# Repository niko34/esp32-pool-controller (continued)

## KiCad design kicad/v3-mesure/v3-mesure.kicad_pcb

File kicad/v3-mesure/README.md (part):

# Carte de mesure du PCB v3 — composants et connexions

> **État : schéma (révision 0.7) et carte routée par script, relus par le relecteur**
> **— toutes les empreintes attribuées, ⚠️ pas encore relu par le relecteur.** Aucune carte n'est dessinée. Ce document est la référence contre
> laquelle le schéma, puis la carte, sont relus.
> Fiche de conception : [`feature-215`](../../specs/features/todo/feature-215-conception-du-pcb-v3.md) ·
> contraintes de fabrication : [`docs/FABRICATION.md`](../../docs/FABRICATION.md).
> Dernière mise à jour : 2026-11-24.

## Les fichiers de ce dossier

| Fichier | Rôle |
|---|---|
| `v3-mesure.kicad_pro` | projet KiCad 9 — c'est lui qu'on ouvre |
| `v3-mesure.kicad_sch` | le schéma, une seule feuille A3 |
| `v3-mesure.kicad_sym` + `sym-lib-table` | les quatre symboles propres à cette carte : ADM3260, module Atlas OEM, prise BNC, connecteur 8 voies |
| `v3-mesure.pretty/` + `fp-lib-table` | les trois empreintes propres à cette carte : `Atlas_OEM`, `BNC_Dosin_801-0080_Coudee`, `Trou_M3_NPTH` |
| `v3-mesure.kicad_pcb` | la carte, **placée et routée** |
| `generer_carte.py` | le script qui écrit la carte ; il prend en entrée la liste des connexions exportée du schéma |
| `v3-mesure.kicad_dru` | la règle d'isolement entre les trois domaines |
| `generer_schema.py` | le script qui a écrit le schéma depuis le tableau des connexions |

**Le schéma (révision 0.7) est tracé avec de vrais fils** — demande de l'utilisateur du
2026-11-24, la révision 0.1 reliait tout par étiquettes. Les alimentations et les masses
passent par les symboles habituels (flèche, masse), comme dans le schéma du v2. Seuls les
quatre signaux du bus rejoignent le connecteur J1 par étiquette, parce que J1 est commun aux
deux voies.

**Ce qui a été vérifié**
- **Dans le KiCad de l'utilisateur** (révision 0.1, 2026-11-24) : contrôle électrique à
  **0 erreur, 0 avertissement**. ⇒ Les noms d'empreintes standard (0402, 0805, 0603,
  SSOP-20, JST XH) existent bien dans ses bibliothèques.
- **En ligne de commande** (révision 0.7, KiCad 9.0.2) : 0 erreur ; la liste des connexions
  que KiCad extrait du schéma est **identique** à celle du tableau de ce document — 21 nets,
  12 broches volontairement en l'air ; rendu regardé en image, sans chevauchement.
  Sur ce poste, le contrôle rend des avertissements d'un seul type : les bibliothèques
  standard de KiCad n'y sont pas installées.

**Ce qui n'est PAS vérifié**
- ✅ Révision 0.2 ouverte dans le KiCad de l'utilisateur le 2026-11-24 : contrôle électrique sans problème. ⚠️ Les révisions 0.3 (C108/C208 retirés) à 0.5 (empreintes du module et de la BNC attribuées) n'y ont pas encore été ouvertes.
- ⚠️ **Aucune des deux empreintes propres n'a été confrontée à une pièce réelle** : elles
  suivent les plans publiés. Avant de commander la carte, imprimer le routage à l'échelle 1
  et y poser un module Atlas et une prise BNC.

⚠️ **`generer_schema.py` réécrit le schéma en entier.** Dès que le schéma est modifié à la
main dans KiCad, ⛔ ne plus le relancer : il écraserait ces modifications.
ℹ️ Le script contient un piège appris à l'usage : KiCad ne relie un fil à un point que si le
fil **s'arrête** à ce point. Un fil qui passe sur une broche sans s'y arrêter n'est pas
relié, même avec un point de jonction dessiné. Le script coupe donc chaque fil à chaque
point de connexion.

## Disposition dans le boîtier (utilisateur, 2026-11-24)

**La carte est montée à l'horizontale (« paysage ») et les prises BNC sortent par le bas.**
⇒ Les deux BNC sont sur le **grand bord du bas**, et ce sont des prises **coudées**.

Conséquences pour le placement, à tenir au routage :
- chaque module Atlas est tourné pour que ses broches 4 (`PRB`) et 5 (`PRB_GND`) regardent
  **vers le bas**, face à sa BNC : c'est ce qui garde la piste de sonde courte ;
- le plan `GND_SONDE` de chaque voie occupe la zone entre le module et le bord du bas
  (Atlas, p. 33 : le plan de sonde couvre le coin des broches 4 et 5) ;
- le connecteur J1 et le côté ESP32 sont à l'opposé, vers le haut ou le centre ;
- ⚠️ le corps des BNC traverse la paroi du bas : **paroi isolante, ou trou plus large que le
  corps** — il ne doit toucher aucun métal relié à la terre (voir « Relecture »).

**Prise retenue** : `C521219` — dosinconn **DOSIN-801-0080**, « BNC jack for PCB », 50 Ω,
coudée, traversante, pièce étendue chez JLCPCB (2 832 en stock chez le distributeur le
2026-11-24). Plan du fabricant (révision A) lu le 2026-11-24 :

| Ce que dit le plan | Valeur |
|---|---|
| Genre | embase femelle (« jack ») ✅ |
| Corps | **laiton nickelé — donc métallique** ; isolant en téflon |
| Fixation | nez **fileté M12 × 0,75**, avec écrou et joint : la prise se **serre sur la paroi** |
| Pattes de corps | 4, Ø 1,2 mm, au pas de **8 mm** (le long de l'axe) × **10 mm** (en travers) |
| Âme | Ø 1 mm, au centre des quatre pattes |
| Hauteur de l'axe au-dessus de la carte | 9,8 mm |
| Longueur totale | 29,5 mm |

⚠️ **Conséquence directe pour le boîtier** : la prise est faite pour être serrée par son écrou
sur la paroi, et son corps est en métal. ⇒ **La paroi du bas doit être isolante** (plastique).
Sur une paroi métallique reliée à la terre, le serrage relierait `GND_SONDE` à la terre et
les deux voies entre elles : l'isolation serait annulée. Le joint, lui, est une bonne chose
en local humide.

**Empreinte** : `v3-mesure:BNC_Dosin_801-0080_Coudee`, nez vers le bas. Âme = plot 1 ; les
quatre pattes de corps = plot 2 (`GND_SONDE`). ✅ Les positions des cinq trous viennent des
cotes écrites sur le plan. ⚠️ Le contour du corps et la position de la paroi (≈ 6,7 mm de
l'âme) sont **mesurés sur le dessin**, pas cotés : à vérifier pièce en main. ⚠️ Perçages
choisis par moi : 1,5 mm pour les pattes, 1,3 mm pour l'âme.

## Dimensions et zones de la carte (proposition du 2026-11-24)

**Règle donnée par l'utilisateur** : le boîtier actuel sert à l'idée générale de disposition ;
les tailles des cartes se fixent librement ; **le boîtier sera adapté ensuite** aux cartes.

**Carte de mesure : 70 × 50 mm, quatre couches, 1,6 mm.** Grand côté à l'horizontale, les
deux BNC sur le bord du bas.

```
        0        17      35      53       70 mm
      0 +----------------------------------+
        | o   COTE ESP32 : J1 au centre  o |   bande de 12 mm :
        |     C101-C104, R101-R102 (x2)    |   connecteur, découplage, rappels
     12 +- - - -[U101]- - - - -[U201]- - - +
        |       barrière : 5,5 mm sans     |   les deux ADM3260 à cheval dessus
   17,5 +- - - - - - - -+   +- - - - - - - +
        |  ILE pH        | | |  ILE ORP    |   5,5 mm sans cuivre entre les îles
        |  C105-C107     | | |  C205-C207  |
        |  R103-R106     | | |  R203-R206  |
        |  [U102 Atlas]  | | |  [U202]     |
        | o [J101 BNC]   | | |  [J201]   o |
     50 +------|---------+---+----|--------+
              16,85             53,15         axes des BNC : entraxe 36,3 mm
```

| Élément | Valeur | Pourquoi |
|---|---|---|
| Largeur | 70 mm | deux îles de 30,8 mm + 5,5 mm entre elles + 1,45 mm de marge de chaque côté |
| Hauteur | 50 mm | bande ESP32 12 mm + barrière 5,5 mm + îles 32,5 mm |
| Entraxe des BNC | **36,3 mm** | celui des deux perçages existants du boîtier : ils peuvent resservir |
| Axe des BNC | à X = 16,85 et 53,15 mm | centre de chaque île |
| Âme des BNC | à 6,0 mm du bord du bas | la paroi intérieure est à ≈ 6,7 mm de l'âme : 0,7 mm de jeu entre carte et paroi |
| Barrière | bande sans cuivre de 5,5 mm, de Y = 12 à 17,5 mm | fiche ADM3260 rév. F ; les deux isolateurs la chevauchent |
| Séparation des voies | bande sans cuivre de 5,5 mm, de X = 32,25 à 37,75 mm | les deux voies ne partagent rien |
| Fixations | 4 trous Ø 3,2 mm **non métallisés**, à 3,5 mm des bords | reliés à rien (relecture) ; cuivre écarté de 2 mm autour |

**Dans chaque île, de haut en bas** : la moitié isolée de l'ADM3260 et ses sept composants ;
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
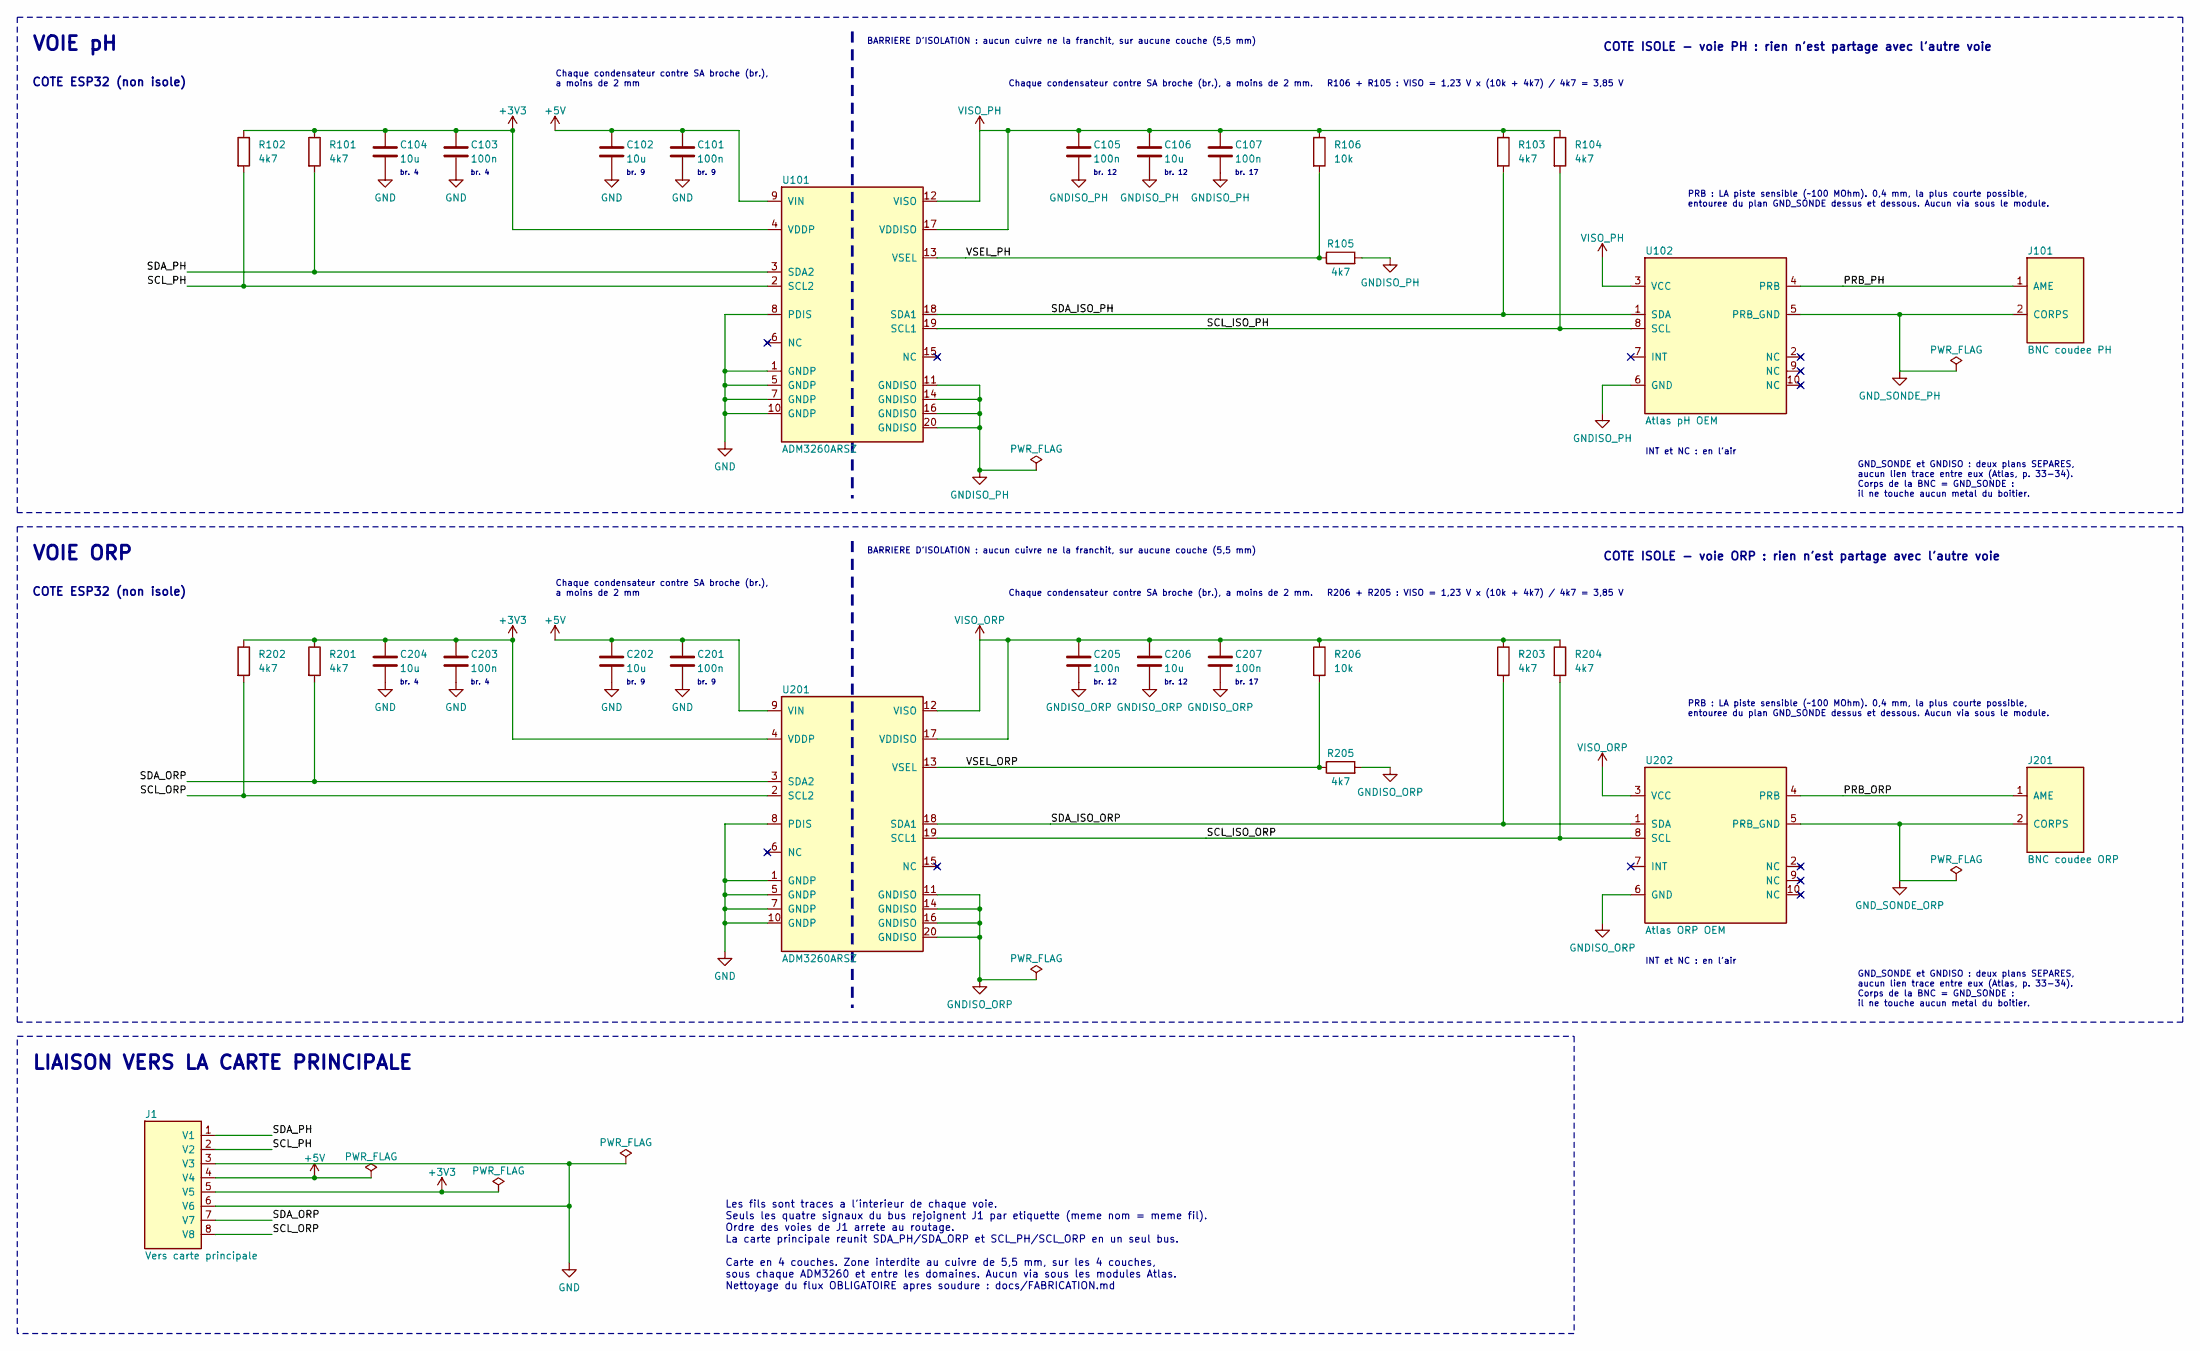
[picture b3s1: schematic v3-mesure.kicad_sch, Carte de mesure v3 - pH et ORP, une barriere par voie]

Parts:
C101, C103, C105, C107, C201, C203, C205, C207: 100n; C_0402_1005Metric; LCSC C1525
C102, C104, C106, C202, C204, C206: 10u; C_0805_2012Metric; LCSC C15850
J1: Vers carte principale; JST_XH_B8B-XH-A_1x08_P2.50mm_Vertical; LCSC C157972
J101: BNC coudee PH; BNC_Dosin_801-0080_Coudee; LCSC C521219
J201: BNC coudee ORP; BNC_Dosin_801-0080_Coudee; LCSC C521219
R101, R102, R103, R104, R105, R201, R202, R203, R204, R205: 4k7; R_0603_1608Metric; LCSC C23162
R106, R206: 10k; R_0603_1608Metric; LCSC C25804
U101, U201: ADM3260ARSZ; SSOP-20_5.3x7.2mm_P0.65mm; LCSC C208558
U102: Atlas pH OEM; Atlas_OEM
U202: Atlas ORP OEM; Atlas_OEM

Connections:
+3V3: C103.1, C104.1, C203.1, C204.1, J1.5 (V5), R101.1, R102.1, R201.1, R202.1, U101.4 (VDDP), U201.4 (VDDP)
+5V: C101.1, C102.1, C201.1, C202.1, J1.4 (V4), U101.9 (VIN), U201.9 (VIN)
/PRB_ORP: J201.1 (AME), U202.4 (PRB)
/PRB_PH: J101.1 (AME), U102.4 (PRB)
/SCL_ISO_ORP: R204.2, U201.19 (SCL1), U202.8 (SCL)
/SCL_ISO_PH: R104.2, U101.19 (SCL1), U102.8 (SCL)
/SCL_ORP: J1.8 (V8), R202.2, U201.2 (SCL2)
/SCL_PH: J1.2 (V2), R102.2, U101.2 (SCL2)
/SDA_ISO_ORP: R203.2, U201.18 (SDA1), U202.1 (SDA)
/SDA_ISO_PH: R103.2, U101.18 (SDA1), U102.1 (SDA)
/SDA_ORP: J1.7 (V7), R201.2, U201.3 (SDA2)
/SDA_PH: J1.1 (V1), R101.2, U101.3 (SDA2)
/VSEL_ORP: R205.1, R206.2, U201.13 (VSEL)
/VSEL_PH: R105.1, R106.2, U101.13 (VSEL)
GND: C101.2, C102.2, C103.2, C104.2, C201.2, C202.2, C203.2, C204.2, J1.3 (V3), J1.6 (V6), U101.1 (GNDP), U101.5 (GNDP), U101.7 (GNDP), U101.8 (PDIS), U101.10 (GNDP), U201.1 (GNDP), U201.5 (GNDP), U201.7 (GNDP), U201.8 (PDIS), U201.10 (GNDP)
GNDISO_ORP: C205.2, C206.2, C207.2, R205.2, U201.11 (GNDISO), U201.14 (GNDISO), U201.16 (GNDISO), U201.20 (GNDISO), U202.6 (GND)
GNDISO_PH: C105.2, C106.2, C107.2, R105.2, U101.11 (GNDISO), U101.14 (GNDISO), U101.16 (GNDISO), U101.20 (GNDISO), U102.6 (GND)
GND_SONDE_ORP: J201.2 (CORPS), U202.5 (PRB_GND)
GND_SONDE_PH: J101.2 (CORPS), U102.5 (PRB_GND)
VISO_ORP: C205.1, C206.1, C207.1, R203.1, R204.1, R206.1, U201.12 (VISO), U201.17 (VDDISO), U202.3 (VCC)
VISO_PH: C105.1, C106.1, C107.1, R103.1, R104.1, R106.1, U101.12 (VISO), U101.17 (VDDISO), U102.3 (VCC)

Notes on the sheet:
VOIE pH
COTE ESP32 (non isole)
COTE ISOLE - voie PH : rien n'est partage avec l'autre voie
BARRIERE D'ISOLATION : aucun cuivre ne la franchit, sur aucune couche (5,5 mm)
br. 9
br. 4
Chaque condensateur contre SA broche (br.), a moins de 2 mm
br. 12
br. 17
PRB : LA piste sensible (~100 MOhm). 0,4 mm, la plus courte possible, entouree du plan GND_SONDE dessus et dessous. Aucun via sous le module.
GND_SONDE et GNDISO : deux plans SEPARES, aucun lien trace entre eux (Atlas, p. 33-34). Corps de la BNC = GND_SONDE : il ne touche aucun metal du boitier.
INT et NC : en l'air
Chaque condensateur contre SA broche (br.), a moins de 2 mm. R106 + R105 : VISO = 1,23 V x (10k + 4k7) / 4k7 = 3,85 V
VOIE ORP
COTE ISOLE - voie ORP : rien n'est partage avec l'autre voie
Chaque condensateur contre SA broche (br.), a moins de 2 mm. R206 + R205 : VISO = 1,23 V x (10k + 4k7) / 4k7 = 3,85 V
LIAISON VERS LA CARTE PRINCIPALE
Les fils sont traces a l'interieur de chaque voie. Seuls les quatre signaux du bus rejoignent J1 par etiquette (meme nom = meme fil). Ordre des voies de J1 arrete au routage. La carte principale reunit SDA_PH/SDA_ORP et SCL_PH/SCL_ORP en un seul bus. Carte en 4 couches. Zone interdite au cuivre de 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

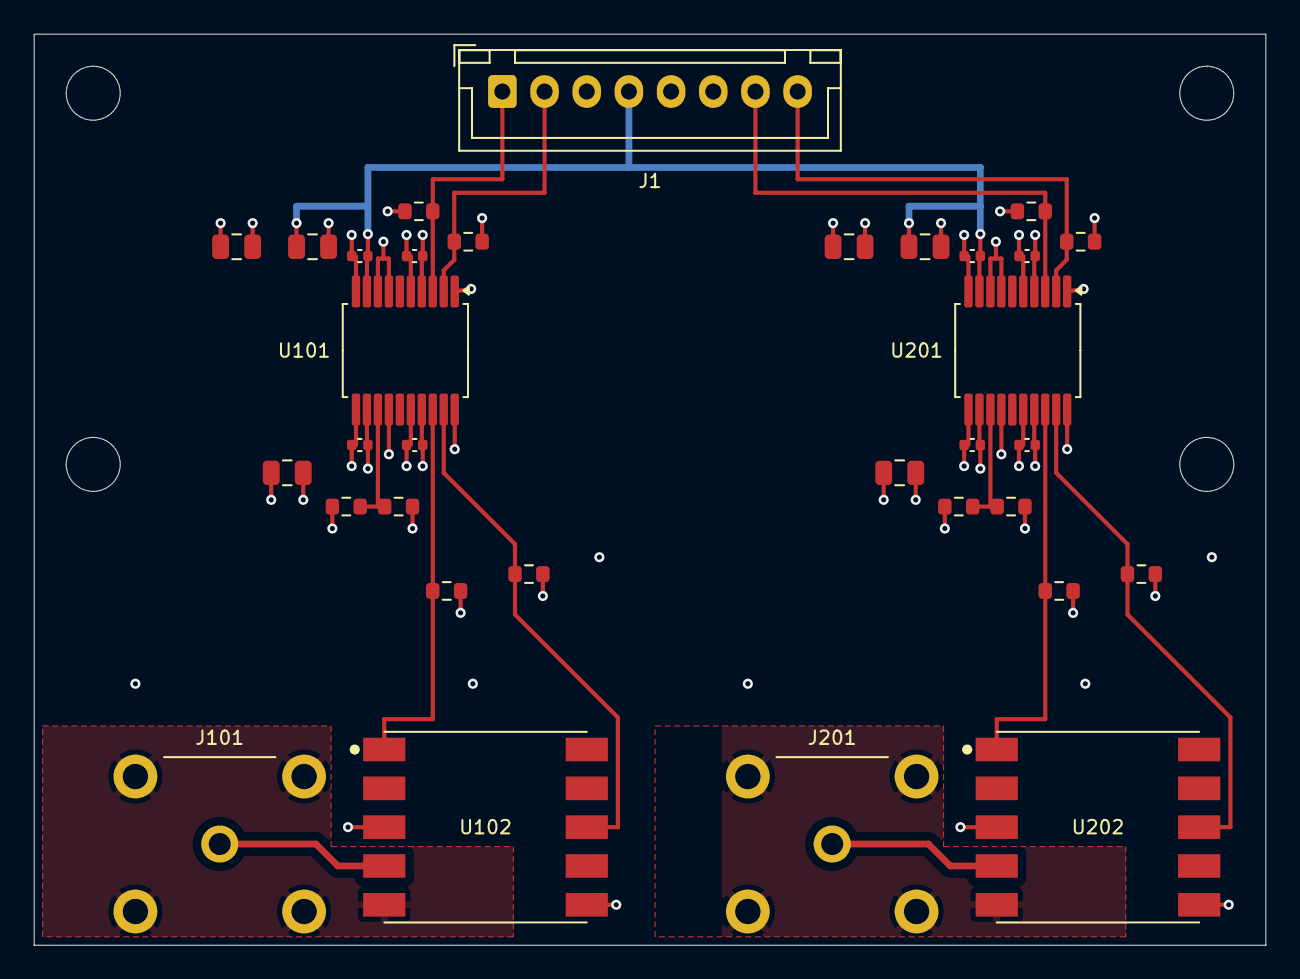
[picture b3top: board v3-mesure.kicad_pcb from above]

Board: 4 copper layers, 73.0 x 54.0 mm, 37 parts (0 on the bottom side), 21 nets.

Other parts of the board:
H1, H2, H3, H4: Trou_M3_NPTH

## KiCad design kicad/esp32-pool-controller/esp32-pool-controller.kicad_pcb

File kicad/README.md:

# Matériel — point d'entrée

Sources KiCad du PCB du contrôleur de piscine.

⚠️ **Les sources de ce dossier sont GELÉES sauf demande explicite** (règle 5 de
[`CLAUDE.md`](../CLAUDE.md)) : on ne modifie ni le schéma ni le routage au fil
d'une tâche logicielle.

⭐ **Avant de modifier une carte du v3** (`v3-principale/`, `v3-mesure-std/`) : lire
[`REGLES-CEM-ET-FIABILITE.md`](REGLES-CEM-ET-FIABILITE.md). Il dit quelles protections chaque
carte porte, pourquoi, et ce qui a déjà été étudié puis écarté. Après la modification :
`python3 scripts/verifier_regles_cartes.py <carte>` — `./scripts/build-jlcpcb.sh` le lance d'office
et refuse de produire les fichiers de fabrication si une règle tombe.

## Fichiers

| Fichier | Rôle |
|---|---|
| `esp32-pool-controller.kicad_sch` · `.kicad_pcb` · `.kicad_pro` | Sources, **versionnées** |
| `SymLib.kicad_sym` · `sym-lib-table` | Bibliothèque de symboles du projet |
| `BOM.xlsx` | **Nomenclature de référence** — ⛔ toute correction se fait ICI |

⛔ **`BOM.csv` est un DÉRIVÉ**, généré par `python3 tools/bom_export.py` depuis le
`.xlsx`, donc ignoré par git. ⚠️ **Ne jamais le corriger à la main** : la prochaine
exécution du script l'écrase.

Les fichiers de fabrication (gerbers, perçage, zips) ne sont **pas** versionnés :
ils se régénèrent avec `./scripts/build-gerbers.sh` (carte v2) ou `./scripts/build-jlcpcb.sh` (cartes v3, avec la liste des pièces et les positions) et deviennent les assets d'une
release `pcb-vX` via `/release-pcb`.

---

## 🔴 Deux défauts MATÉRIELS non résolus — à instruire avant toute révision du PCB

**Ils ont été sortis du backlog logiciel le 2026-10-17**, sur décision de
l'utilisateur : *« ces investigations sont du ressort de l'humain qui conçoit le
PCB »*. ⛔ **Clôturées ne veut pas dire résolues** — elles attendent une personne
avec des instruments, pas une session de travail.

### 1. Perturbation de mode commun sur les électrodes pH/ORP
[`specs/features/done/feature-137-perturbation-de-mode-commun-sur-les-electrodes.md`](../specs/features/done/feature-137-perturbation-de-mode-commun-sur-les-electrodes.md)

Le pH brut est **anti-corrélé et presque à deux niveaux**, et **la voie ORP voit la
même perturbation** : les deux électrodes subissent un **mode commun**. Mécanisme
suspecté : couplage électrique via le verre (~100 MΩ) avec les **courants de fuite
de la pompe de filtration** — mesure nettement meilleure sur batterie.

⚠️ **Ce que ça coûte aujourd'hui** : le 2026-10-16, l'eau réelle était à **pH 8**
et la sonde lisait **6,9**. Une correction de **+1,00** a dû être posée — **le
double de l'ancienne borne**, retirée pour la rendre possible (ADR-0114, v2.82.0).
⛔ **Le logiciel ne corrige pas ce défaut, il le COMPENSE** — sur la grandeur même
qui décide des injections d'acide.

⇒ C'est la **seule voie** qui assainirait le signal **à la source**.

### 2. Transitoire de reprise de filtration
[`specs/features/done/feature-069-investigation-materielle-sonde-ph.md`](../specs/features/done/feature-069-investigation-materielle-sonde-ph.md)

Trois matins consécutifs (02-04/09/2026), même signature : brut **normal** à la
remise en circulation, plongeon à **5,60-5,71** quelques minutes après, retour à la
normale en **30 à 48 min**, ⚠️ **l'ORP plongeant en parallèle** (−56 à −74 mV).

⛔ **Les cinq hypothèses restent ouvertes** (chambre désamorcée · bulles piégées ·
effet électrique au démarrage · eau réellement acide · sonde vieillissante).

⭐ **Le relevé qui tranche** : **deux bandelettes simultanées**, une au **bassin** et
une au **refoulement**, à **t+2** et **t+15 min** après la reprise. C'est le seul
qui sépare « l'eau est réellement acide » de « la sonde lit faux ». ⚠️ Tout le reste
en découle.
⛔ **Préalable de sécurité** : régulation pH en **manuel** pendant toute
manipulation de sonde.

### Lié, et toujours ouvert côté logiciel
[`bug-135`](../specs/features/todo/bug-135-butee-brute-ph-se-declenche-sur-une-lecture-isolee.md)
— la butée de sécurité brute se déclenche sur ces lectures isolées. ⚠️ **Même
cause** : tant que le mode commun est là, le logiciel doit composer avec un signal
qui alterne entre deux niveaux.

## Références
- [ADR-0012 — mapping GPIO du PCB v2](../docs/adr/0012-mapping-gpio-pcb-v2.md)
- [ADR-0097 — Le filtre lisse, le dosage juge](../docs/adr/0097-le-filtre-lisse-le-dosage-juge.md) — ce que le logiciel fait du bruit, faute de pouvoir le supprimer
- [feature-097 — Seuil de stabilité sur données terrain](../specs/features/done/feature-097-seuil-de-stabilite-sur-donnees-terrain.md) — la campagne qui **caractérise** le bruit (⛔ sans l'expliquer)

Pour passer la commande : [étapes et options JLCPCB](COMMANDE-JLCPCB.md).

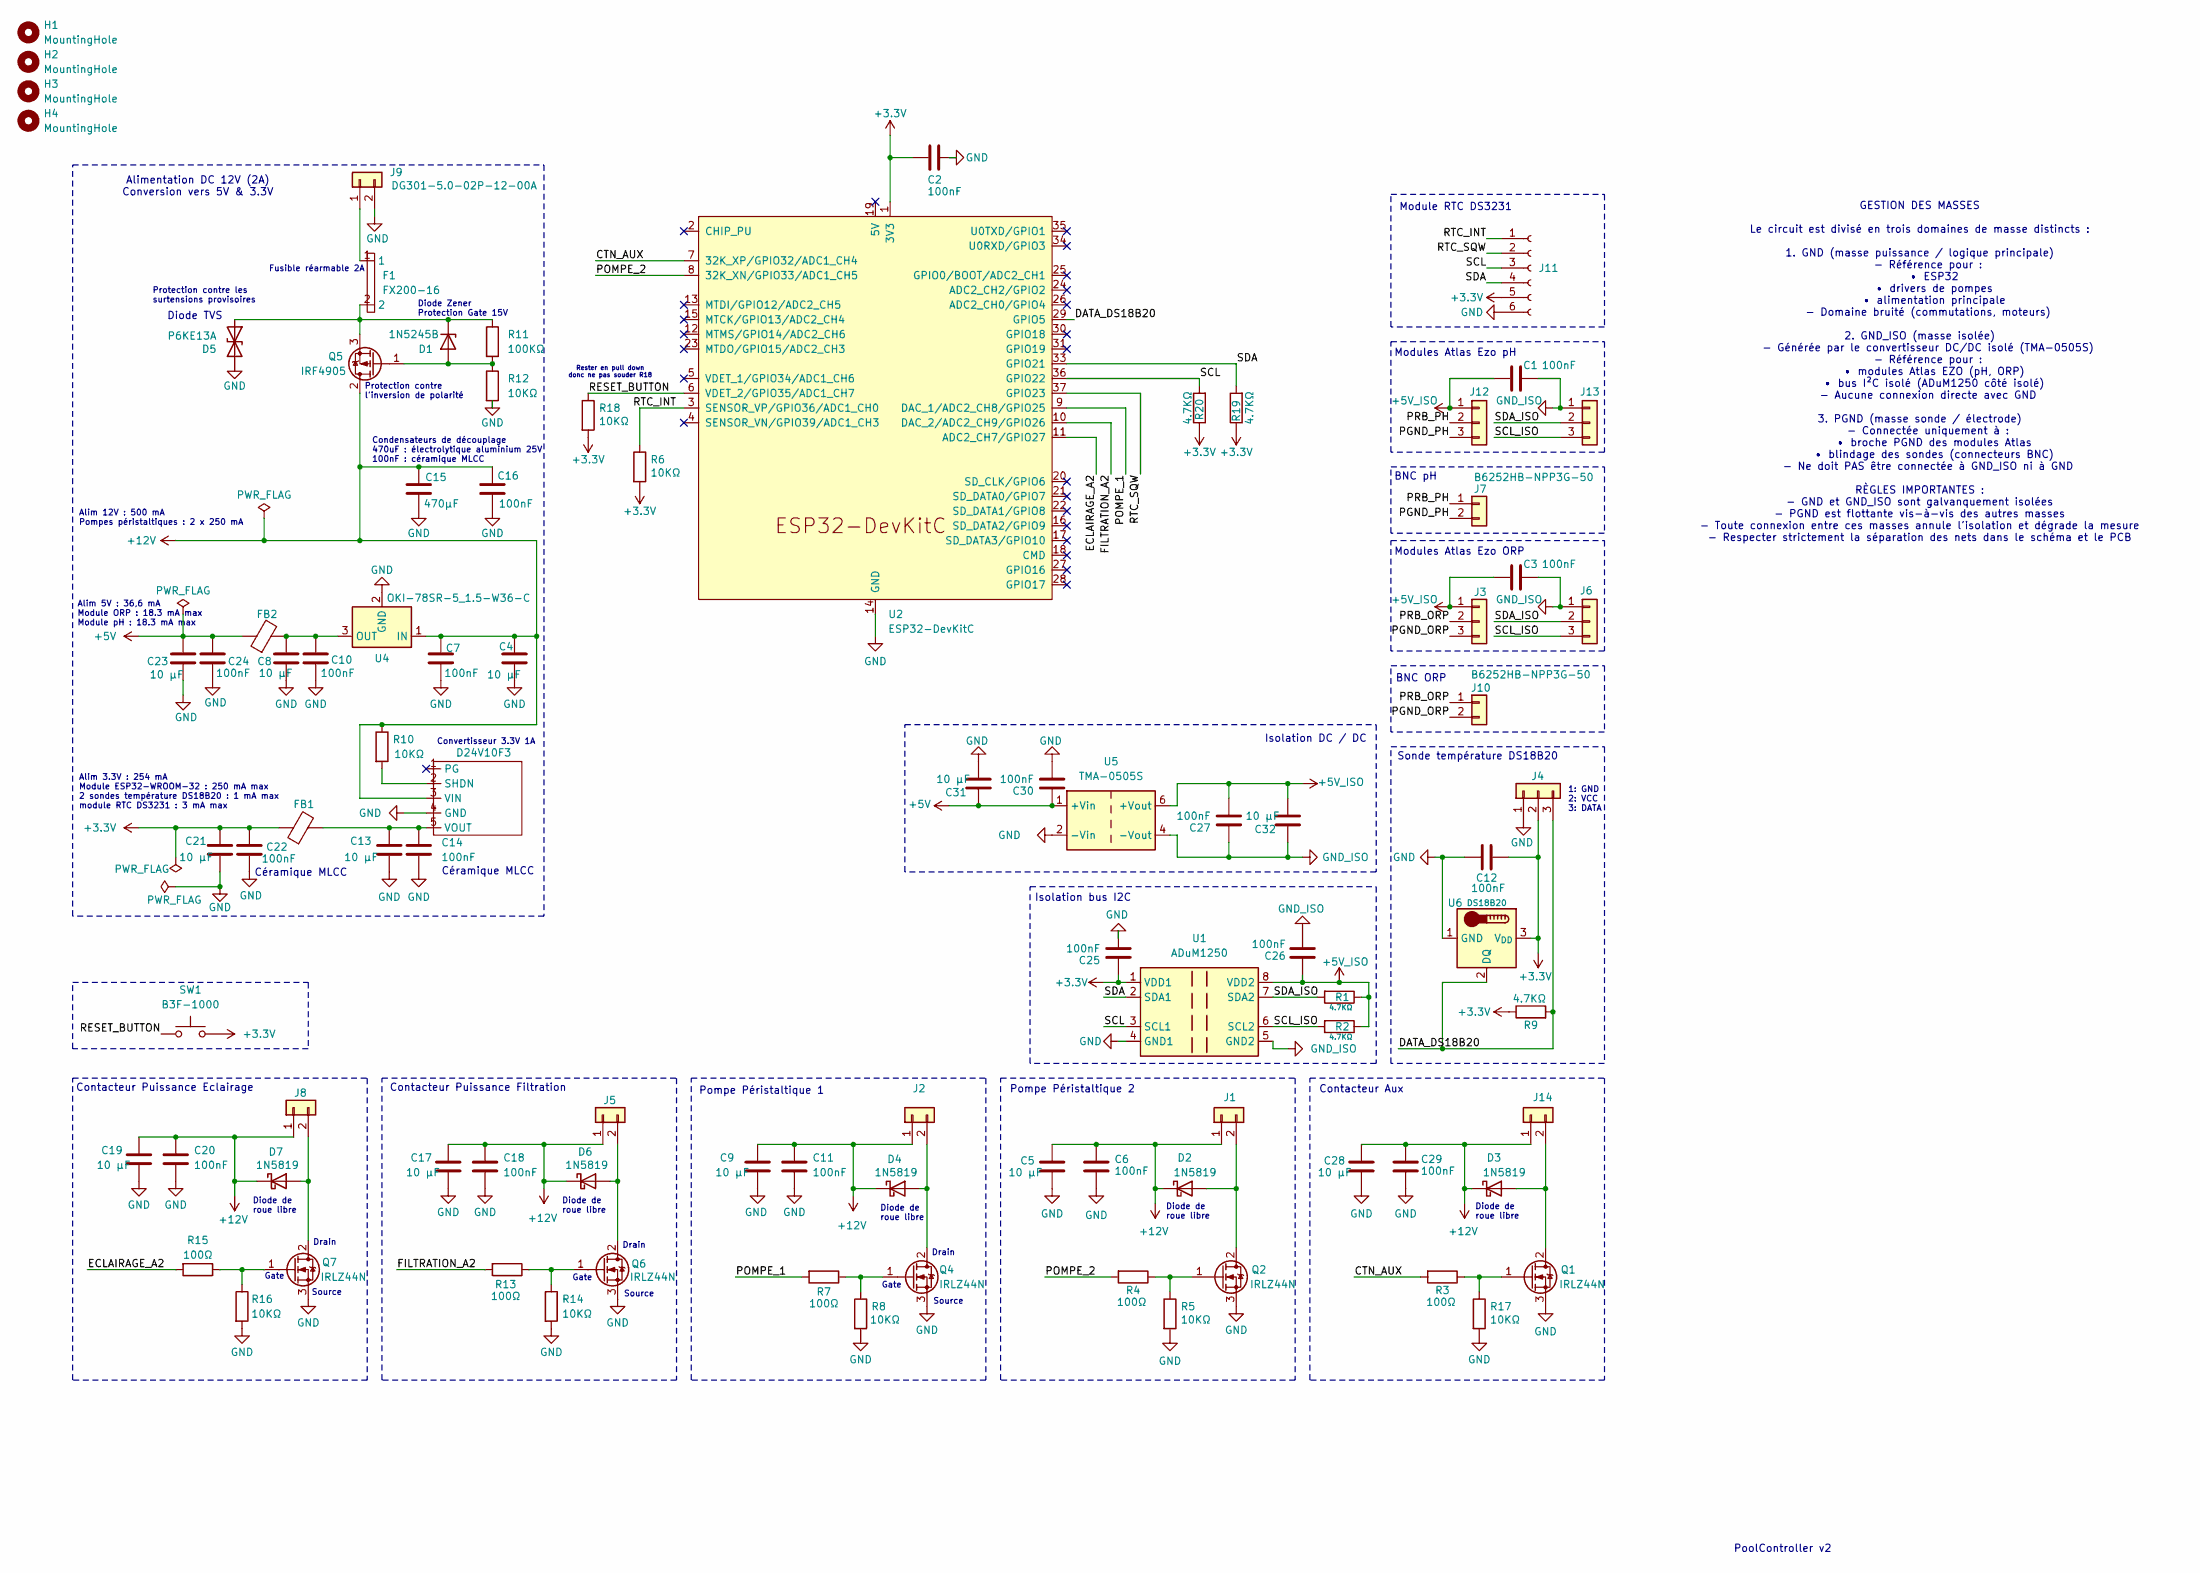
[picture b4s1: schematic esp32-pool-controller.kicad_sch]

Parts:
C1, C2, C3, C6, C7, C10, C11, C12, C14, C16, C18, C20, C22, C24, C25, C26, C27, C29, C30: 100nF; C_Disc_D3.8mm_W2.6mm_P2.50mm
C4, C5, C8, C9, C13, C17, C19, C21, C23, C28, C31, C32: 10 µF; C_Disc_D6.0mm_W4.4mm_P5.00mm
C15: 470µF; CP_Radial_D10.0mm_P5.00mm
D1: 1N5245B; D_DO-35_SOD27_P7.62mm_Horizontal
D2, D3, D4, D6, D7: 1N5819; D_DO-15_P10.16mm_Horizontal
D5: P6KE13A; D_DO-15_P10.16mm_Horizontal
F1: FX200-16; Fuse_Bourns_MF-RHT200
FB1, FB2: BBPY00321611601Y00; R_1206_3216Metric
H1, H2, H3, H4: MountingHole; MountingHole_3.2mm_M3
J1, J2, J5, J8, J9, J14: DG301-5.0-02P-12-00A; Altech_AK100_1x02_P5.00mm
J3, J6, J12, J13: Conn_01x03; PinSocket_1x03_P2.54mm_Vertical
J4: DG301-5.0-03P-12-00AH; JST_XH_B3B-XH-A_1x03_P2.50mm_Vertical
J7, J10: B6252HB-NPP3G-50; BNC_Amphenol_B6252HB-NPP3G-50_Horizontal
J11: Conn_01x06_Socket; PinSocket_1x06_P2.54mm_Vertical
Q1, Q2, Q4, Q6, Q7: IRLZ44N; TO-220-3_Vertical
Q5: IRF4905; TO-220-3_Vertical
R1, R2, R9, R19, R20: 4.7KΩ; R_Axial_DIN0207_L6.3mm_D2.5mm_P10.16mm_Horizontal
R3, R4, R7, R13, R15: 100Ω; R_Axial_DIN0207_L6.3mm_D2.5mm_P10.16mm_Horizontal
R5, R6, R8, R10, R12, R14, R16, R17, R18: 10KΩ; R_Axial_DIN0207_L6.3mm_D2.5mm_P10.16mm_Horizontal
R11: 100KΩ; R_Axial_DIN0207_L6.3mm_D2.5mm_P10.16mm_Horizontal
SW1: B3F-1000; SW_PUSH_6mm
U1: ADuM1250; DIP-8_W7.62mm
U2: ESP32-DevKitC
U3: D24V10F3; Pololu_D24V10F3
U4: OKI-78SR-5_1.5-W36-C; Converter_DCDC_Murata_OKI-78SR_Vertical
U5: TMA-0505S; Converter_DCDC_TRACO_TMA-05xxS_12xxS_Single_THT
U6: DS18B20; TO-92_Inline

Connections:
+3.3V: C2.2, C12.2, C21.1, C22.1, C25.1, FB1.1, J4.2, J11.5, R6.2, R9.1, R18.2, R19.1, R20.1, SW1.2, U1.1 (VDD1), U2.1 (3V3), U6.3 (V_{DD})
+5V: C23.1, C24.1, C30.1, C31.2, FB2.1, U5.1 (+Vin)
+5V_ISO: C1.1, C3.1, C26.1, C27.2, C32.1, J3.1, J12.1, R1.1, R2.1, U1.8 (VDD2), U5.6 (+Vout)
+12V: C4.1, C5.1, C6.1, C7.1, C9.1, C11.1, C15.1, C16.1, C17.1, C18.1, C19.1, C20.1, C28.1, C29.1, D2.1 (K), D3.1 (K), D4.1 (K), D6.1 (K), D7.1 (K), J1.1, J2.1, J5.1, J8.1, J14.1, Q5.2 (D), R10.1, U3.3 (VIN), U4.1 (IN)
/CTN_AUX: R3.2, U2.7 (32K_XP/GPIO32/ADC1_CH4)
/DATA_DS18B20: J4.3, R9.2, U2.29 (GPIO5), U6.2 (DQ)
/ECLAIRAGE_A2: R15.2, U2.11 (ADC2_CH7/GPIO27)
/FILTRATION_A2: R13.2, U2.10 (DAC_2/ADC2_CH9/GPIO26)
/PGND_ORP: J3.3, J10.2
/PGND_PH: J7.2, J12.3
/POMPE_1: R7.2, U2.9 (DAC_1/ADC2_CH8/GPIO25)
/POMPE_2: R4.2, U2.8 (32K_XN/GPIO33/ADC1_CH5)
/PRB_ORP: J3.2, J10.1
/PRB_PH: J7.1, J12.2
/RESET_BUTTON: R18.1, SW1.1, U2.6 (VDET_2/GPIO35/ADC1_CH7)
/RTC_INT: J11.1, R6.1, U2.3 (SENSOR_VP/GPIO36/ADC1_CH0)
/RTC_SQW: J11.2, U2.37 (GPIO23)
/SCL: J11.3, R20.2, U1.3 (SCL1), U2.36 (GPIO22)
/SCL_ISO: J6.3, J13.3, R2.2, U1.6 (SCL2)
/SDA: J11.4, R19.2, U1.2 (SDA1), U2.33 (GPIO21)
/SDA_ISO: J6.2, J13.2, R1.2, U1.7 (SDA2)
GND: C2.1, C4.2, C5.2, C6.2, C7.2, C8.2, C9.2, C10.2, C11.2, C12.1, C13.2, C14.2, C15.2, C16.2, C17.2, C18.2, C19.2, C20.2, C21.2, C22.2, C23.2, C24.2, C25.2, C28.2, C29.2, C30.2, C31.1, D5.2 (A2), J4.1, J9.2, J11.6, Q1.3 (S), Q2.3 (S), Q4.3 (S), Q6.3 (S), Q7.3 (S), R5.2, R8.2, R12.2, R14.2, R16.2, R17.2, U1.4 (GND1), U2.14 (GND), U2.32 (GND), U2.38 (GND), U3.4 (GND), U4.2 (GND), U5.2 (-Vin), U6.1 (GND)
GND_ISO: C1.2, C3.2, C26.2, C27.1, C32.2, J6.1, J13.1, U1.5 (GND2), U5.4 (-Vout)
unnamed: D1.2 (A), Q5.1 (G), R11.2, R12.1
unnamed: D1.1 (K), D5.1 (A1), F1.2, Q5.3 (S), R11.1
unnamed: D2.2 (A), J1.2, Q2.2 (D)
unnamed: D3.2 (A), J14.2, Q1.2 (D)
unnamed: D4.2 (A), J2.2, Q4.2 (D)
unnamed: D6.2 (A), J5.2, Q6.2 (D)
unnamed: D7.2 (A), J8.2, Q7.2 (D)
unnamed: F1.1, J9.1
unnamed: Q1.1 (G), R3.1, R17.1
unnamed: Q2.1 (G), R4.1, R5.1
unnamed: Q4.1 (G), R7.1, R8.1
unnamed: Q6.1 (G), R13.1, R14.1
unnamed: Q7.1 (G), R15.1, R16.1
unnamed: R10.2, U3.2 (SHDN)
unnamed: C13.1, C14.1, FB1.2, U3.5 (VOUT)
unnamed: C8.1, C10.1, FB2.2, U4.3 (OUT)

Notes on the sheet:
Contacteur Aux
Alimentation DC 12V (2A) Conversion vers 5V & 3.3V
Protection contre l'inversion de polarité
Contacteur Puissance Eclairage
Pompe Péristaltique 2
Module RTC DS3231
Céramique MLCC
Diode de roue libre
PoolController v2
Gate
Modules Atlas Ezo ORP
Contacteur Puissance Filtration
Drain
Rester en pull down donc ne pas souder R18
Sonde température DS18B20
Diode Zener Protection Gate 15V
Alim 3.3V : 254 mA Module ESP32-WROOM-32 : 250 mA max 2 sondes température DS18B20 : 1 mA max module RTC DS3231 : 3 mA max
GESTION DES MASSES Le circuit est divisé en trois domaines de masse distincts : 1. GND (masse puissance / logique principale) - Référence pour : • ESP32 • drivers de pompes • alimentation principale - Domaine bruité (commutations, moteurs) 2. GND_ISO (masse isolée) - Générée par le convertisseur DC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
Source
1: GND 2: VCC 3: DATA
Alim 12V : 500 mA Pompes péristaltiques : 2 x 250 mA
Diode TVS
Alim 5V : 36,6 mA Module ORP : 18.3 mA max Module pH : 18.3 mA max
Isolation bus I2C
Modules Atlas Ezo pH
Convertisseur 3.3V 1A
Pompe Péristaltique 1
Isolation DC / DC
Fusible réarmable 2A
Condensateurs de découplage 470uF : électrolytique aluminium 25V 100nF : céramique MLCC
BNC ORP
BNC pH
Protection contre les surtensions provisoires

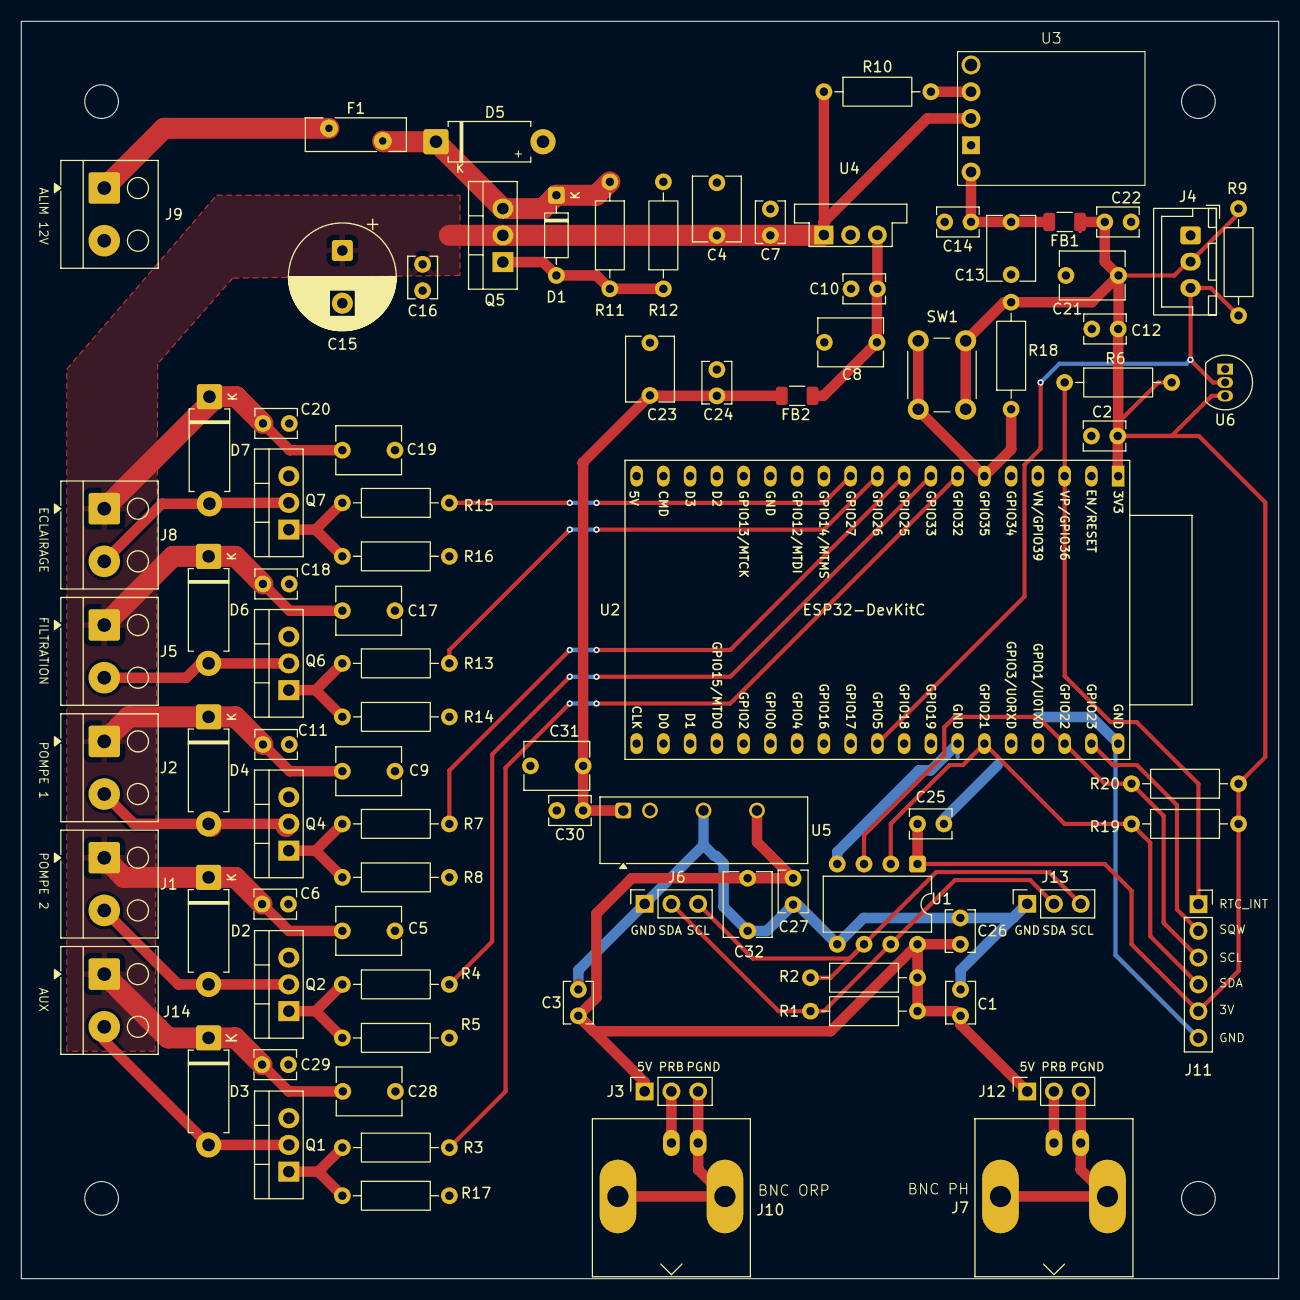
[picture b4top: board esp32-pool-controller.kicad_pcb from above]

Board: 2 copper layers, 119.4 x 119.4 mm, 93 parts (0 on the bottom side), 39 nets.

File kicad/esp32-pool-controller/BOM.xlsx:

Reference | Qty | Value | Comment | Link
C1,C2,C3,C6,C7,C10,C11,C12,C14,C16,C18,C20,C22,C24,C25,C26,C27,C29,C30 | 19 | K104K10X7RF5UL2 | 100nF céramique X7R 10% 2.54mm | https://www.tme.eu/fr/details/k104k10x7rf5ul2/condensateurs-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
C4,C5,C8,C9,C13,C17,C19,C21,C23,C28,C31,C32 | 12 | FG20X7R1H106KRT06 | 10µF céramique mlcc X7R 10% 5.1mm | https://www.tme.eu/fr/details/fg20x7r1h106krt06/condensateur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
C15 | 1 | ECA1EHG471B | 470µF Electrolytique 25V | https://www.tme.eu/fr/details/eca1ehg471b/condensateurs-elec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
D1 | 1 | 1N5245B | Diode: Zener; 0,5W; 15V | https://www.tme.eu/fr/details/1n5245btr/diodes-zener-tht/onsemi/
D2,D3,D4,D6,D7 | 5 | 1N5819 | Diode: redressement Schottky; THT; 40V; 1A; DO15; Ufmax: 900mV | https://www.tme.eu/fr/details/1n5819-dio/diodes-schottky-tht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
D5 | 1 | P6KE13A |  | https://www.tme.eu/fr/details/p6ke13a-dio/diodes-unidirectio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
F1 | 1 | 30R185UU | Fusible PPTC 30VDC courant maintien 1.85A THT 5.1mm | https://fr.farnell.com/littelfuse/30r185uu/polyfuse-ptc-radi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
FB1,FB2 | 2 | BBPY00321611601Y00 |  | https://www.tme.eu/fr/details/bbpy00321611601y00/ferrites-pe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
J1,J2,J5,J8,J9,J14 | 6 | DG301-5.0-02P-12-00A |  | https://www.tme.eu/fr/details/dg301-5.0-2p12/blocs-de-bornes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
J3,J6,J11,J12,J13 | 5 | DS1002-03-1*20131 | Pour connecteur ESP32, module RTC, module pH, module ORPÉ | https://www.tme.eu/fr/details/zl307-1x20/batis-de-prises-et-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
J4 | 1 | DG301-5.0-03P-12-00AH | Connecteur JST 3P
J7,J10 | 2 | B6252HB-NPP3G-50 |  | https://www.tme.eu/fr/details/b6252hb-npp3g-50/connecteurs-b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
Q1,Q2,Q4,Q6,Q7 | 5 | IRLZ44NPBF | Transistor: N-MOSFET; unipolaire; 55V; 41A; 83W; TO220AB | https://www.tme.eu/fr/details/irlz44npbf/transistors-tht-a-c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
Q5 | 1 | IRF4905PBF | Transistor: P-MOSFET; unipolaire; -55V; -74A; 200W; TO220AB | https://www.tme.eu/fr/details/irf4905pbf/transistors-a-canal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
R1,R2,R9,R19,R20 | 5 | 4.7KΩ | Idéalement metal film 1% 0,25W. Si 1% pas disponible, 5% possible.
R3,R4,R7,R13,R15 | 5 | 100Ω | Idéalement metal film 1% 0,25W. Si 1% pas disponible, 5% possible.
R5,R6,R8,R10,R12,R14,R16,R17,R18 | 9 | 10KΩ | Idéalement metal film 1% 0,25W. Si 1% pas disponible, 5% possible.
R11 | 1 | 100KΩ | Idéalement metal film 1% 0,25W. Si 1% pas disponible, 5% possible.
SW1 | 1 | B3F-1000 |  | https://www.tme.eu/fr/details/b3f-1000/micro-interrupteurs-t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
U1 | 1 | ADuM1250 |  | https://www.tme.eu/fr/details/adum1250arz/circuits-integres-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
 | 1 | Adaptateur SOP8 vers DIP8 |  | https://www.gotronic.fr/art-adaptateur-so8-dil8-19701.htm?sr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
U2 | 1 | ESP32-DevKitC-VE | Avec de la PSRAM | https://fr.aliexpress.com/item/1005004686938288.html?spm=a2g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
U3 | 1 | D24V10F3 |  | https://www.tme.eu/fr/details/pololu-2830/onduleurs/pololu/3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
U4 | 1 | OKI-78SR-5_1.5-W36-C
U5 | 1 | TMA-0505S |  | https://www.tme.eu/fr/details/tma0505s/convertisseurs-dc-dc/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
U6 | 1 | DS18B20+ |  | https://www.tme.eu/fr/details/ds18b20+/transmetteurs-de-temp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
 | 1 | Module Atlas EZO pH |  | https://www.digikey.fr/fr/products/detail/atlas-scientific/E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
 | 1 | Module Atlas EZO ORP |  | https://www.digikey.fr/fr/products/detail/atlas-scientific/E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
 | 1 | Sonde pH connecteur BNC
 | 1 | Sonde ORP connecteur BNC
 | 1 | Module RTC DS3231 |  | https://fr.aliexpress.com/item/1005010435328928.html?spm=a2g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
 | 0 | module ADC ADS1115
 | 1 | Finder 22.32.0.012.4340 | Si contrôle filtration : Contacteur rail DIN 12V / 220V 25A
 | 1 | Finder 22.32.0.012.4340 | Si contrôle éclairage : Contacteur rail DIN 12V / 220V 25A
 | 2 | Pompe PŽristaltique 12V 90ml/min 12V-S10B avec tuyau en BPT PharMed (plus simpl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 |  | https://fr.aliexpress.com/item/1005008568962671.html?spm=a2g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
 | 1 | Si tuyau pompe pas en Pharmed : tuyau Pharmed ˆ la coupe |  | https://fr.aliexpress.com/item/1005005939700189.html?spm=a2g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
 | 2 | Raccord ou clapet anti-retour en PVDF vers tuyau injection 4x6. Taille 1/8'' |  | https://fr.aliexpress.com/item/32721015040.html?spm=a2g0o.or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
 | 2 | Tuyau 4x6mm en PE pour raccorder tuyau pompe au bidon de produit |  | https://eau2.fr/tube-pe-chlore-et-ph/597-49-tube-pe-4x6mm-ch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
 | 1 | Alimentation Rail DIN : Mean Well HDR-30-12 2A |  | https://www.amazon.fr/dp/B071KXJPYB?ref=ppx_yo2ov_dt_b_fed_a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
 | 2 | Clapet d'injection raccord 1/2'' Chlore ou pH |  | https://eau2.fr/analyseur-pieces-detachees-astralpool/404-cl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
 | 1 | Collecteur piscine porte sonde diamtre 50 |  | https://jardiboutique.com/fr/regulateur-ph-rx/15015-collecte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
 | 2 | Filtre aspiration pompe doseuse |  | https://eau2.fr/aspiration-du-chlore-liquide-et-ph-moins/733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
